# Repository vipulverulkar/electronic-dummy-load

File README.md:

# Double Electronic Load Project

LM358-based double electronic load.

## Motivation

I needed a quick, cheap and simple method of testing the capacity of a rather large batch of small Li-ion cells to bin them and assemble a larger battery.

The testers I obtained to measure the actual capacity (ZB2L3) had a simple 15 Ohm resistor as a load. Measuring capacity with a resistor can be imprecise, because the current drops together with the voltage as the cell discharges and this may give greater capacity than you would normally expect.

There are multiple recipes out there of producing a constant-current load using an op-amp, a voltage reference and a MOSFET. The ones I found interesting are:

* [DIY POWERFUL ELECTRONIC LOAD WITH LM358](https://www.youtube.com/watch?v=7ahOXYocZ3Y) by [KD CREATIVITY](https://www.youtube.com/@kdcreativity6201)
* [Simple battery capacity meter](https://www.youtube.com/watch?v=puiJUjyRxHI) by [AKA KASYAN](https://www.youtube.com/@AkaKasyanEng)
* [Adjustable Constant Current Load - Linear](https://hackaday.io/project/186915-adjustable-constant-current-load-linear) by [Manu](https://hackaday.io/GearBliss)

They however use only one half of LM358 dual op-amp and I had a limited amount of them lying around vs other stuff like TL431 I had bought by the dozens previously, so it made sense to use both halves.

I based my circuit on the one by [AKA KASYAN](https://www.youtube.com/@AkaKasyanEng) and simply doubled everything except the op-amp. You can also use the second half of LM358 to drive a fan depending on the MOSFET temperature, but my discharge current will barely warm up the heatsink, so instead I opted for two semi-independent load cells.

## Parts Used

The parts here don't have to be very precise or even genuine, as long as they're working.

I frequently order stuff from AliExpress in large excess of what I actually need for a project in case some particular seller decides to sell counterfeit that doesn't work properly.

The PCB was ordered as usually from JLCPCB.

Not all parts of the [schematic](images/double-electronic-load.kicad_sch.pdf) are described here.

Some notable part choices:

* The heatsink used is 50x25x10mm, anodized aluminium. Bought for around $0.3 a piece.

* `Q1` and `Q2` are SFP50N06, about $2.5/10 pcs.

* `R10` and `R20` are low-inductance, part no. BPR56, bought for $1.40/10 pcs. Don't have to be low-inductance, but they are more compact than regular 5W resistors.

* `J1`, `J2` and `J3` are LZ128 5mm screw terminal blocks I had lying around, but can be of any other type.

The rest of the parts were in total about $5.

## Using the Load

### Connecting with ZB2L3

The load requires a 7-9V DC 10-20mA power supply for a more stable operation, compared to 5V DC the ZB2L3 uses, so powering it off USB isn't advised. ZB2L3 has a regulator, so it shouldn't be affected by the increased voltage.

* The `L+` terminal must be connected to either one of `R`/`IN+` inputs of the ZB2L3 tester.

* The battery/current source positive lead must be connected to the second `R`/`IN+` input of ZB2L3.

* The `GND` terminal must be tied together with the opposite `R` input of ZB2L3 (i.e. the one closer to `IN-`).

* The battery/current source negative lead must be connected to the `IN-` input of ZB2L3.

* +7-9V DC power supply is connected to both the `VCC` terminal of the load and `DC5V` pad on the underside of the ZB2L3 tester.

### Adjusting the Current

Load current is adjusted using `R4` and `R14` trimmer pots.

## Photos

Early working prototype:

PCBs from JLCPCB:

Fully populated PCB:

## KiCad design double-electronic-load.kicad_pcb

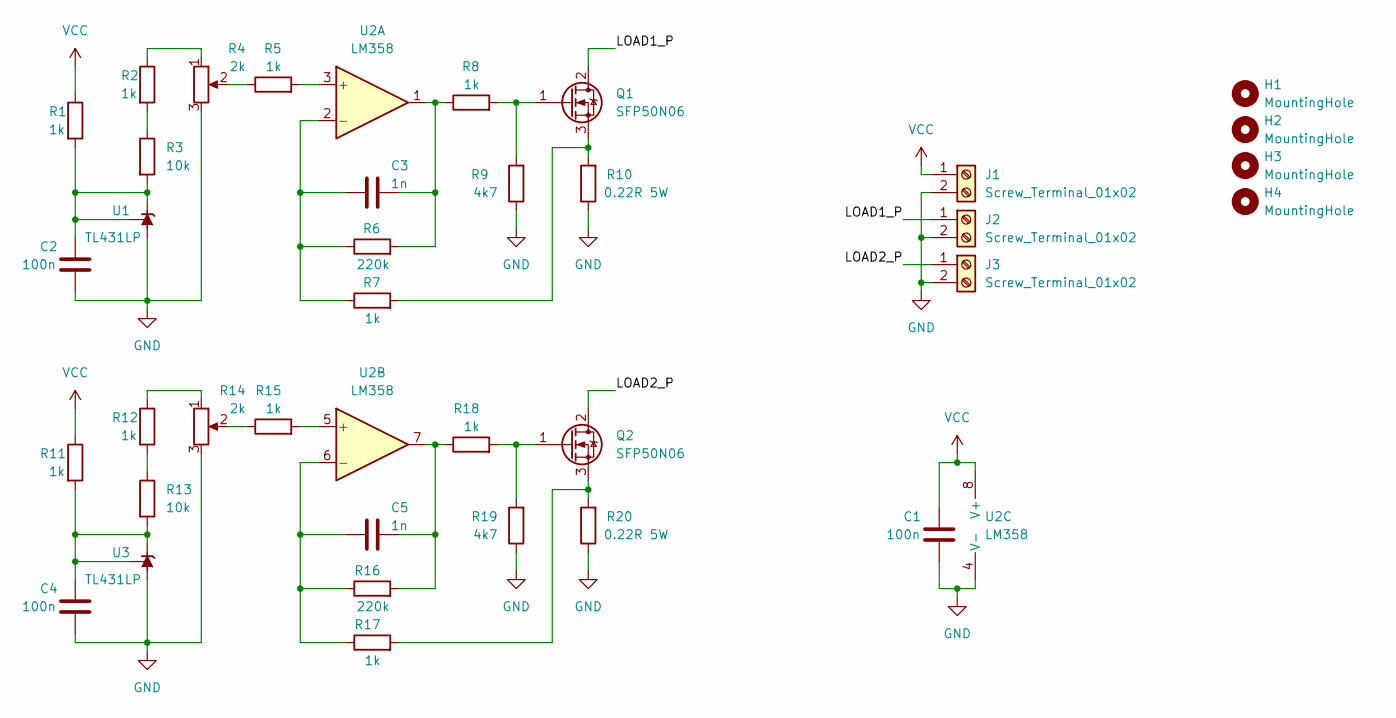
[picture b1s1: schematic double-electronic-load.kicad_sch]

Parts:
C1, C2, C4: 100n; C_Disc_D5.1mm_W3.2mm_P5.00mm
C3, C5: 1n; C_Disc_D5.1mm_W3.2mm_P5.00mm
H1, H2, H3, H4: MountingHole; MountingHole_3.2mm_M3
J1, J2, J3: Screw_Terminal_01x02; Lianzhe_LZ128_D-508_2
Q1, Q2: SFP50N06; TO-220-3_Vertical
R1, R2, R5, R7, R8, R11, R12, R15, R17, R18: 1k; R_Axial_DIN0207_L6.3mm_D2.5mm_P7.62mm_Horizontal
R3, R13: 10k; R_Axial_DIN0207_L6.3mm_D2.5mm_P7.62mm_Horizontal
R4, R14: 2k; Potentiometer_Bourns_3296W_Vertical
R6, R16: 220k; R_Axial_DIN0207_L6.3mm_D2.5mm_P7.62mm_Horizontal
R9, R19: 4k7; R_Axial_DIN0207_L6.3mm_D2.5mm_P7.62mm_Horizontal
R10, R20: 0.22R 5W; R_Box_L14.0mm_W5.0mm_P9.00mm
U1, U3: TL431LP; TO-92L_HandSolder
U2: LM358; DIP-8_W7.62mm_LongPads

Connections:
/LOAD1_P: J2.1, Q1.2 (D)
/LOAD2_P: J3.1, Q2.2 (D)
GND: C1.2, C2.1, C4.1, J1.2, J2.2, J3.2, R4.3, R9.1, R10.1, R14.3, R19.1, R20.1, U1.2 (A), U2.4 (V-), U3.2 (A)
unnamed: C2.2, R1.2, R3.2, U1.1 (REF), U1.3 (K)
unnamed: C3.1, R6.1, R7.1, U2.2 (-)
unnamed: C3.2, R6.2, R8.1, U2.1
unnamed: C4.2, R11.2, R13.2, U3.1 (REF), U3.3 (K)
unnamed: C5.1, R16.1, R17.1, U2.6 (-)
unnamed: C5.2, R16.2, R18.1, U2.7
unnamed: Q1.1 (G), R8.2, R9.2
unnamed: Q1.3 (S), R7.2, R10.2
unnamed: Q2.1 (G), R18.2, R19.2
unnamed: Q2.3 (S), R17.2, R20.2
unnamed: R2.1, R4.1
unnamed: R2.2, R3.1
unnamed: R4.2, R5.1
unnamed: R5.2, U2.3 (+)
unnamed: R12.1, R14.1
unnamed: R12.2, R13.1
unnamed: R14.2, R15.1
unnamed: R15.2, U2.5 (+)
VCC: C1.1, J1.1, R1.1, R11.1, U2.8 (V+)

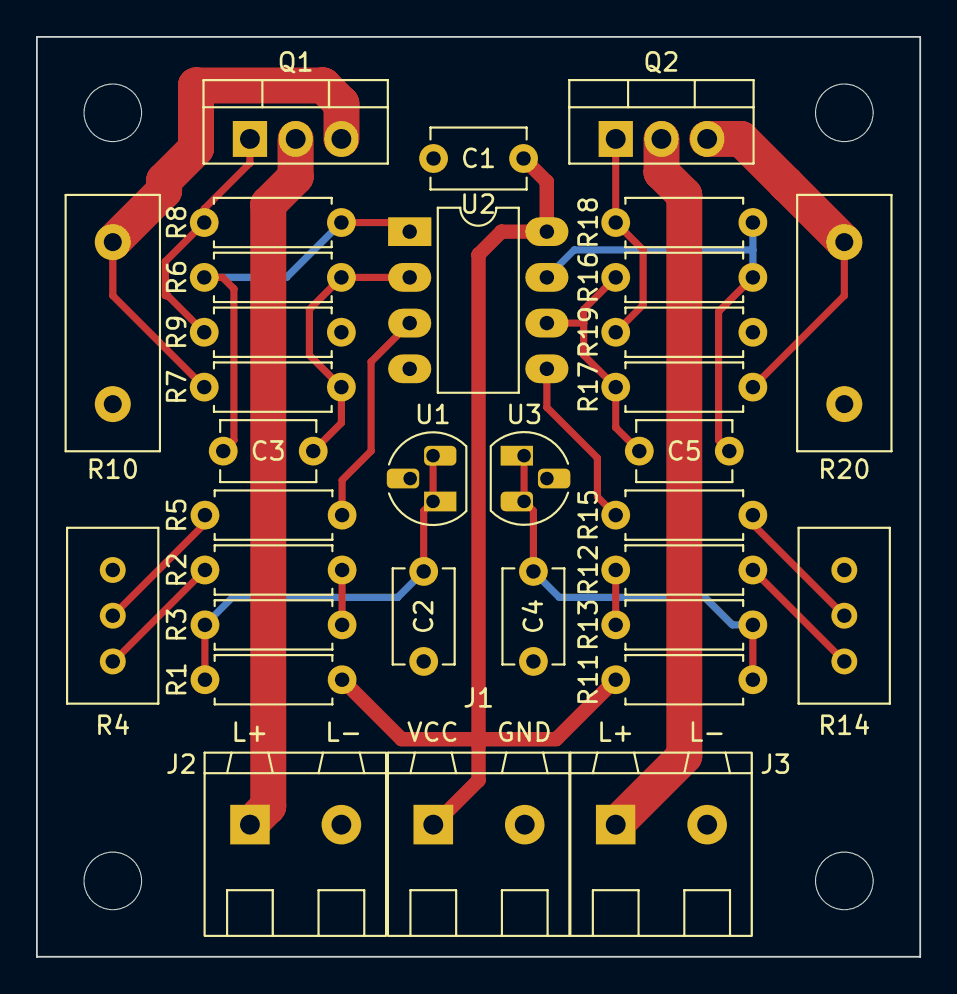
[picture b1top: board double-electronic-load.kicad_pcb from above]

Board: 2 copper layers, 49.1 x 51.1 mm, 37 parts (0 on the bottom side), 22 nets.

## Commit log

2022-09-19 Add revision to PCB
2022-09-20 Gerbers
2023-01-31 Minor cleanup
2023-02-02 Readme, photos
2023-02-02 Add project license

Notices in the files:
double-electronic-load.kicad_pcb:
(C) 2022 VMACHINIST, AKA KASYAN
